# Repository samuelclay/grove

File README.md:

Grove
=====

Mailing list: grove-electronics@googlegroups.com

# Boards

1) Main board - Teensy shield
    - 4 x 3 pins for 144/m 5m strips on trunk
    - 4 x 5 pins (power + rgb) for dispatcher board
    - 3 pins (power + data) for breathing sensor
    - Power switch
    - PTC fuse + zener diode
    - 4 pins for buck converter, 12V -> 5V
    
2) Sensor board
    - 3 pins from mainboard (power, data)
    - Proximity sensor (SI1143x)
    - IR motion detector
    - "breathing" sensor
    - active LEDs

3) Dispatcher board
    - 4 x 5 pins input (power + rgb)
    - 4 PicoBucks (six pins in, six pins out)
    - 16 x 6 pin RGB LEDs (r±, g±, b±)

# Concerns

1) Power
    - 12V deep cycle marine batteries
    - Charging circuit
    - Solar array
    - Delivering 12V to each tree (voltage drop)
2) Firmware
    - Performance over time
    - Running 4x trunks vs 1 trunk 4 times
3) Lighting
    - Soldering high current LEDs
    - 144/m 5m vs splicing power

# Timeline

- May 31: Initial meeting
- June 8th: Dispatcher board rev #1 sent to printer
- June 9th: Main board rev #1 sent to printer
- June 10th: Sensor board rev #1 sent to printer
- July 1st: Boards return from printer, soldering begins
- July 6th: Final board revisions sent to printer
- July 27th: Final boards return from printer, soldering begins
- August 20th: Installation begins on playa
- August 28th: Burning Man begins

# Useful links:

Grove proposal: https://docs.google.com/presentation/d/1Oe51Et6uq_moFoTw9EoB07Vlh8WwSTc89PW6PQpZ1io/edit#slide=id.g12e5fa7d1f_0_1
Grove budget: https://docs.google.com/spreadsheets/d/1ltcCgIae5ANJpvHL2A5ckWDxvADcpXeD_jZIF5hPCvg/edit#gid=0
Prototypes and earlier installation: https://cambridge.nuvustudio.com/studios/grove#tab-proposal-url

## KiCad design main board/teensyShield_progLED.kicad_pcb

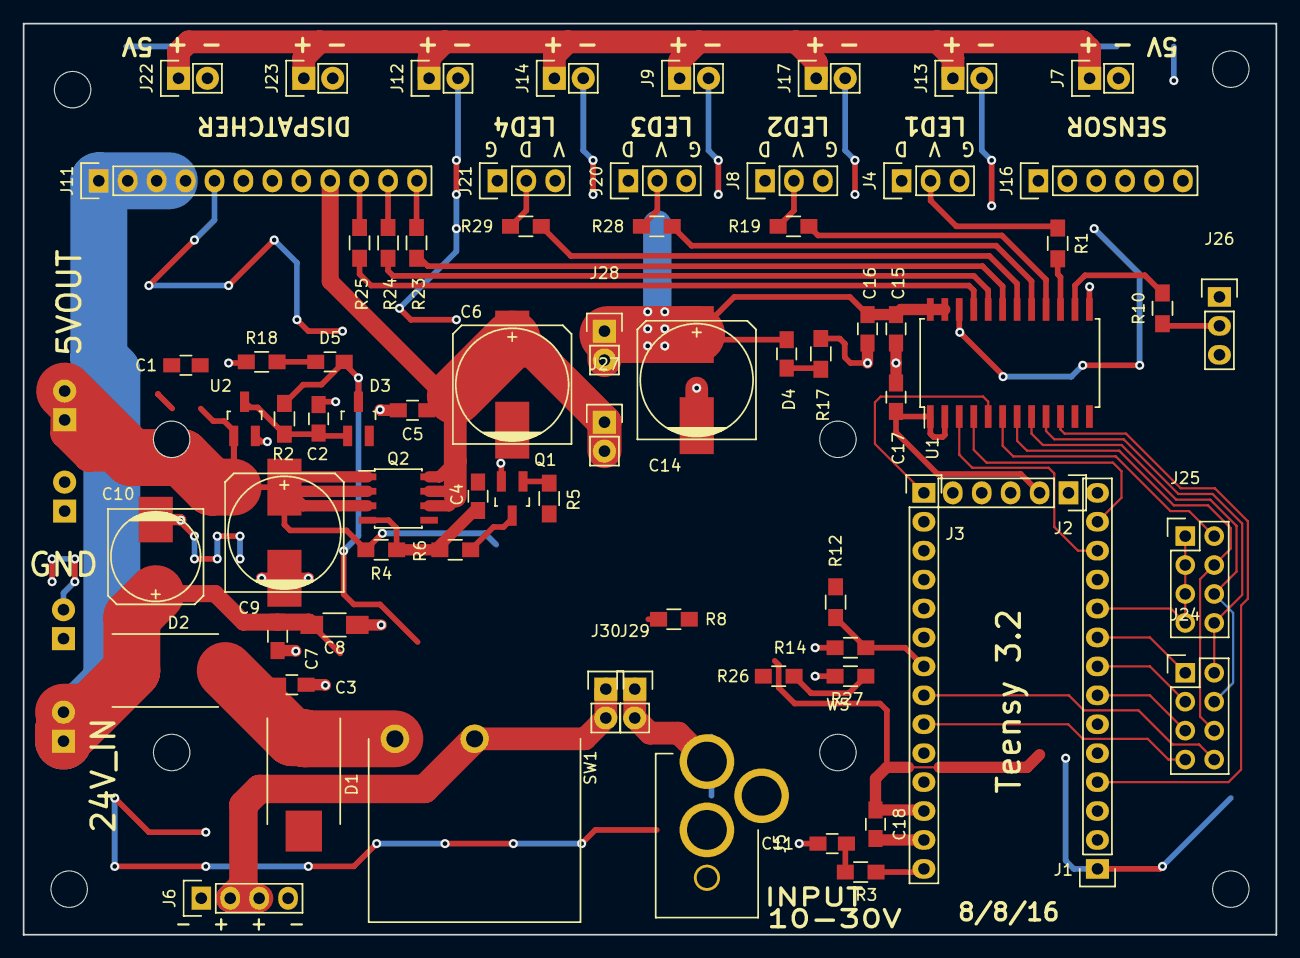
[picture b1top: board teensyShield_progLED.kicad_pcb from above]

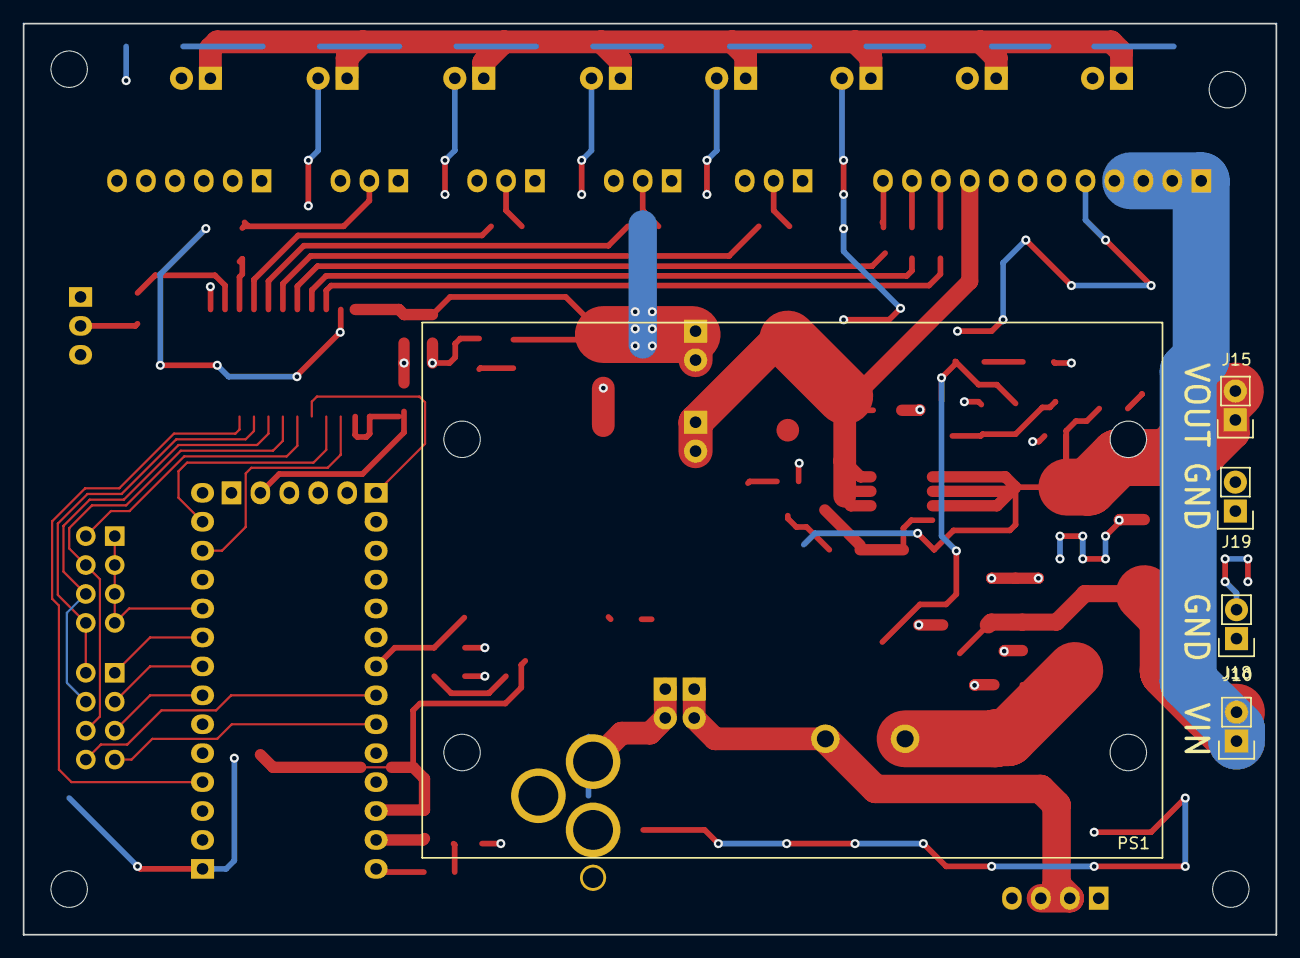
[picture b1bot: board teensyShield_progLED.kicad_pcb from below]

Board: 2 copper layers, 110.0 x 80.0 mm, 85 parts (5 on the bottom side), 52 nets.

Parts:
C1, C2, C3, C5, C7, C11, C15, C16, C17, C18: 1u, 0805; C_0805_HandSoldering
C4: DNS; C_0805_HandSoldering
C6, C10, C14: 1000u, 10V; c_elec_10x10
C8: 10u, 1206; C_1206_HandSoldering
C9: 220u, 35V; c_elec_8x10
D1: TVS; DO-214AB_Handsoldering
D2: SL44HE3_A/H; DO-214AB_Handsoldering
D3: PMEG2005ET,215; SOT-23_DIODE_Handsoldering
D4: BLUE; C_0805_HandSoldering
D5: GRN; C_0805_HandSoldering
J1, J3: CONN_01X14; Pin_Header_Straight_1x14
J2: CONN_01X05; Pin_Header_Straight_1x05
J4, J8, J20, J21, J26: CONN_01X03; Pin_Header_Straight_1x03
J5: BARREL_JACK; PJ-050AH
J6: CONN_01X04; Pin_Header_Straight_1x04
J7, J9, J10, J12, J13, J14, J15, J17, J18, J19, J22, J23, J27, J28, J29, J30: CONN_01X02; Pin_Header_Straight_1x02
J11: CONN_01X12; Pin_Header_Straight_1x12
J16: CONN_01X06; Pin_Header_Straight_1x06
J24, J25: CONN_02X04; Pin_Header_Straight_2x04
PS1: PS_BUCK_MODULE; TC43200
Q1: Q_NMOS_GSD; SOT-23_Handsoldering
Q2: Q_PMOS_SO8; SOIC-8_3.9x4.9mm_Pitch1.27mm
R1, R10, R17, R19, R28, R29: 220; R_0805_HandSoldering
R2: 0; R_0805_HandSoldering
R3, R5, R8, R18: DNS; R_0805_HandSoldering
R4, R12, R14: 10k; R_0805_HandSoldering
R6: 100; R_0805_HandSoldering
R23, R24, R25: 10; R_0805_HandSoldering
R26, R27: 1MEG; R_0805_HandSoldering
SW1: SPST; R1966ABLKBLKFR
U1: SN74LVC8T245PWR; SOIC-24_7.5x15.4mm_Pitch1.27mm
U2: MCP1700T-3302E/TT; SOT-23_Handsoldering
W1, W2, W3, W4, W5, W6, W7, W8: TEST_1P; MountingHole_3.2mm_M3

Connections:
+3V3: C17.1, C18.1, D3.1, D5.2, J2.2, J3.12, R2.1, R8.2, U1.1, U1.2
+5V: C1.1, C10.1, C11.1, J15.1, J15.2, Q2.1, Q2.2, Q2.3, R3.2, R4.2, U2.1
+5VP: C14.1, C15.1, C16.1, D4.2, J4.1, J7.1, J8.1, J9.1, J12.1, J13.1, J14.1, J16.1, J17.1, J20.1, J21.1, J22.1, J23.1, J26.1, J28.1, J28.2, R12.2, U1.23, U1.24
/3V3REG: C2.1, D3.2, R2.2, U2.3
/5V_LSW: C4.1, C5.1, C6.1, J11.9, J27.1, J27.2, Q2.5, Q2.6, Q2.7, Q2.8
/24V_IN: J5.1, J29.1, J29.2
/24V_IN_J: J6.2, J6.3, J30.1, J30.2, SW1.2
/24V_IN_SWITCHED: C3.1, D1.1, D2.2, SW1.1
/24V_IN_SW_RVP: C7.1, C8.1, C9.1, D2.1, J10.1, J10.2, J11.1, J11.2, J11.3, J11.4, R26.2
/CLK_5V: J11.12, R23.1
/CS_5V: J11.10, R25.1
/D4K: D4.1, R17.2
/D5K: D5.1, R18.2
/LED1_5V_STEM: R10.2, U1.14
/LED3_3V3: J24.2, J25.8, U1.9
/LED3_5V: R1.2, U1.15
/LED4_3V3: J25.2, U1.6
/LED4_5V: R29.2, U1.18
/LED5_3V3: J24.4, J25.6, U1.8
/LED5_5V: R19.2, U1.16
/LED8_3V3: J24.6, J25.4, U1.7
/LED8_5V: R28.2, U1.17
/LED_DOUT1: J4.2, R1.1
/LED_DOUT2: J8.2, R19.1
/LED_DOUT3: J20.2, R28.1
/LED_DOUT4: J21.2, R29.1
/LED_DOUT5: J26.2, R10.1
/MOSI_5V: J11.11, R24.1
/P0_RX1: J1.2, J16.5
/P1_TX1: J1.3, J16.4
/P2_LED1: J1.4, U1.10
/P2_P23: J3.11, J16.3
/P5_LED8: J1.7, J24.5
/P6_LED5: J1.8, J24.3
/P7_LED3: J1.9, J24.1
/P8_LED4: J1.10, J25.1, J25.3, J25.5, J25.7
/P10_CS: J1.12, U1.3
/P10_CS_5V: R25.2, U1.21
/P11_MOSI: J1.13, U1.4
/P11_MOSI_5V: R24.2, U1.20
/P13_SCK: J3.1, U1.5
/P14_SCK_5V: R23.2, U1.19
/P15_RES: J3.3, J3.4
/P18: J3.6, Q1.1, R5.2, R8.1
/P19_A5: J3.7, R12.1, R14.2
/P20_A6: R26.1, R27.2
/P20_LED6: J3.8, J24.8
/P21_LED7: J3.9, J24.7
/Q2G: C4.2, Q2.4, R4.1, R6.2
/Q2GR: Q1.3, R6.1
/VIN: J3.14, R3.1
GND: C1.2, C2.2, C3.2, C5.2, C6.2, C7.2, C8.2, C9.2, C10.2, C11.2, C14.2, C15.2, C16.2, C17.2, C18.2, D1.2, J1.1, J2.3, J3.13, J4.3, J5.2, J5.3, J6.1, J6.4, J7.2, J8.3, J9.2, J11.5, J11.6, J11.7, J11.8, J12.2, J13.2, J14.2, J16.2, J16.6, J17.2, J18.1, J18.2, J19.1, J19.2, J20.3, J21.3, J22.2, J23.2, J26.3, Q1.2, R5.1, R14.1, R17.1, R18.1, R27.1, U1.11, U1.12, U1.13, U1.22, U2.2, W1.1, W2.1, W3.1, W4.1, W5.1, W6.1, W7.1, W8.1

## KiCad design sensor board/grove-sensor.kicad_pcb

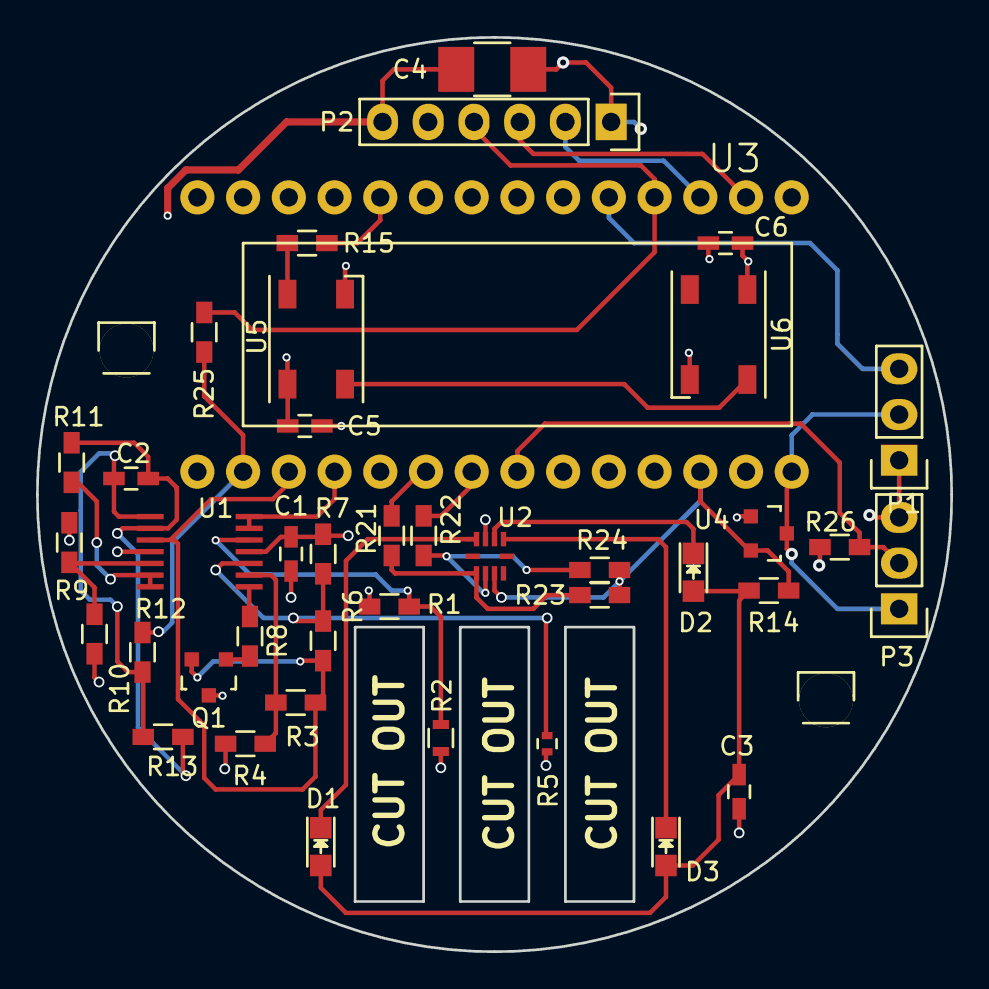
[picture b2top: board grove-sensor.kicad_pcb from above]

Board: 4 copper layers, 50.8 x 50.8 mm, 42 parts (0 on the bottom side), 31 nets.

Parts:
C1, C5, C6: 0.1uF; C_0603_HandSoldering
C2: 10uF; C_0603_HandSoldering
C3: 15uF; C_0603_HandSoldering
C4: 100uF; C_1210_HandSoldering
D1, D2, D3: LED; LED_0805
P1, P3: CONN_01X03; Pin_Header_Straight_1x03
P2: CONN_01X06; Pin_Header_Straight_1x06
P5, P6: CONN_01X01; Pin_Header_Straight_1x01
Q1: Q_NPN_BEC; SOT-23
R1, R7, R9, R10, R23, R24, R26: 10k; R_0603_HandSoldering
R2: 10k; R_0603
R3, R8, R11, R12: 2k; R_0603_HandSoldering
R4: 165k; R_0603_HandSoldering
R5: THERM; R_0402
R6: 1; R_0603_HandSoldering
R13: 4.3k; R_0603_HandSoldering
R14: 30; R_0603_HandSoldering
R15: 300; R_0603_HandSoldering
R21, R22, R25: 0; R_0603_HandSoldering
U1: ADD8704; TSSOP-14
U2: SI1143
U3: Teensy_3.1; Teensy-3.1
U4: MCP1700; SOT-23
U5, U6: WS2812B; LED_WS2812B-PLCC4

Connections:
+5V: C1.1, C4.1, C5.1, C6.1, P1.2, P2.6, P3.1, Q1.3, R1.1, R7.1, R9.1, U1.4, U3.26, U4.3, U5.1, U6.1
/3.3V: R14.1, R23.2, R24.2, U2.3, U3.24, U4.2
/LED_IN: R15.1, U5.4
/OUT: R12.2, R25.2, U3.14
/PIR_IN: P3.2, R26.2, U3.20
/SCL: R22.2, U3.19
/SDA: R21.2, U3.18
/SENSITIVITY: R9.2, R10.1, U1.12
/TEMP_OUT: U1.6, U1.7, U3.16
/V_RAW: Q1.2, R3.1, R6.1, U1.10, U3.15
GND: C1.2, C3.1, C4.2, C5.2, C6.2, P1.1, P2.1, P2.5, P3.3, R2.2, R4.2, R5.2, R10.2, R26.1, U1.11, U2.8, U3.25, U3.27, U4.1, U5.3, U6.3
unnamed: C2.1, R12.1, R13.2, U1.8
unnamed: C2.2, R11.2, R13.1, U1.9
unnamed: C3.2, D1.2, D2.2, D3.2, R14.2
unnamed: D1.1, U2.9
unnamed: D2.1, U2.7
unnamed: D3.1, U2.6
unnamed: P1.3, U3.3
unnamed: P2.2, U3.1
unnamed: P2.3, U3.0
unnamed: P2.4, R25.1, U3.2
unnamed: Q1.1, R8.1
unnamed: R1.2, R2.1, U1.5
unnamed: R3.2, R4.1, U1.2
unnamed: R5.1, R6.2, R7.2, U1.3
unnamed: R8.2, U1.1
unnamed: R11.1, U1.13, U1.14
unnamed: R15.2, U3.8
unnamed: R21.1, R23.1, U2.1
unnamed: R22.1, R24.1, U2.2
unnamed: U5.2, U6.4

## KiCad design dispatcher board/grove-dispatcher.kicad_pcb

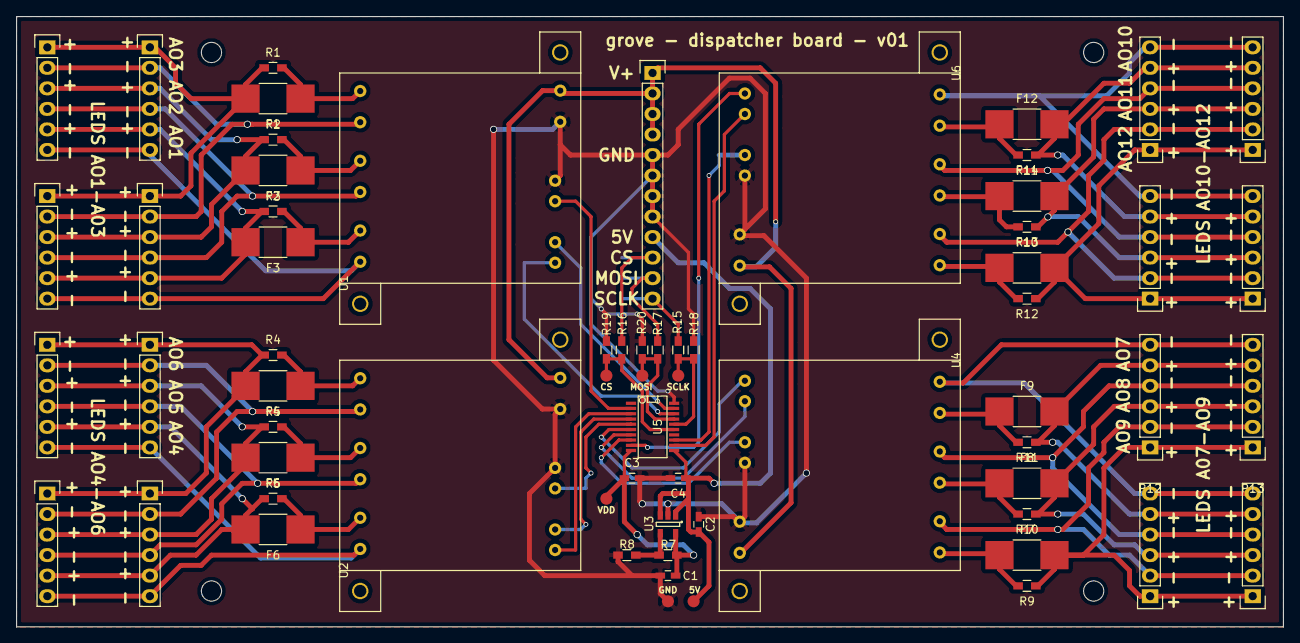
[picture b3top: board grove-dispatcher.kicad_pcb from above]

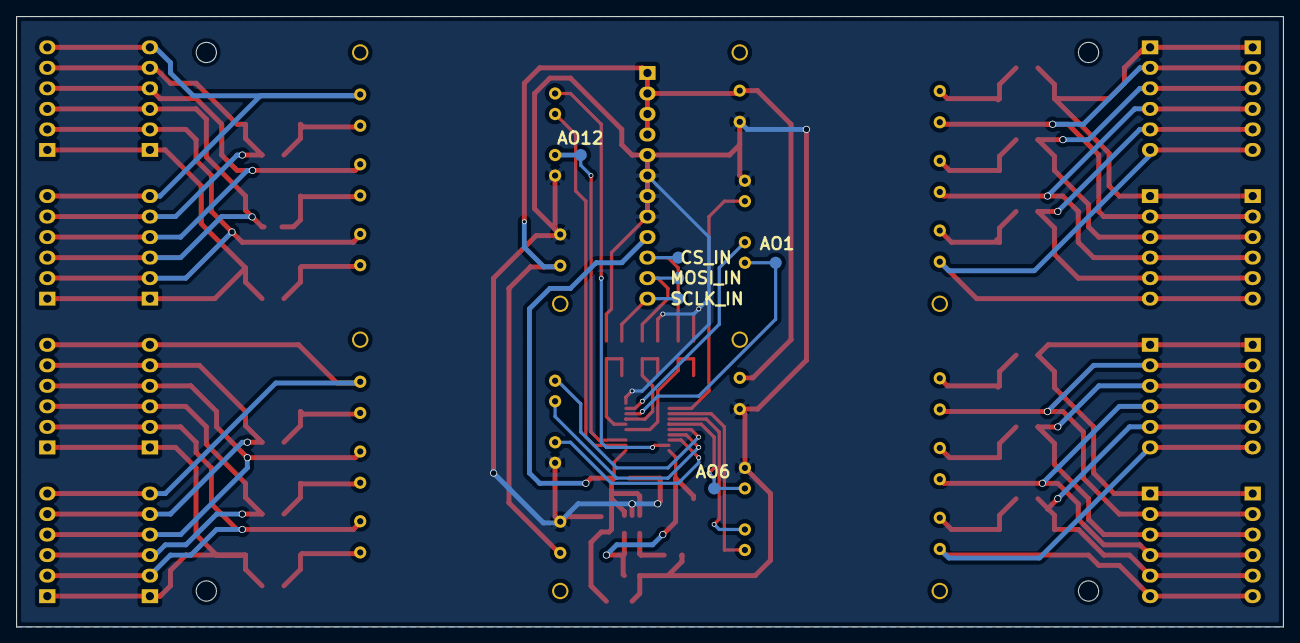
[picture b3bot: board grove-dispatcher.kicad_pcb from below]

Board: 2 copper layers, 156.8 x 75.6 mm, 71 parts (6 on the bottom side), 59 nets.

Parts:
C1, C2, C3, C4: 1uF; C_0603_HandSoldering
F1, F2, F3, F4, F5, F6, F7, F8, F9, F10, F11, F12: PTC; R_1812_HandSoldering
P1: CONN_01X12; Pin_Header_Straight_1x12
P2, P3, P4, P5, P6, P7, P8, P9, P10, P11, P12, P13, P14, P15, P16, P17: CONN_01X06; Pin_Header_Straight_1x06
R1, R2, R3, R4, R5, R6, R9, R10, R11, R12, R13, R14: 0; R_0603_HandSoldering
R7: ?ohm; R_0603_HandSoldering
R8: ?ohms; R_0603_HandSoldering
R15, R16, R17: 10ohm; R_0603_HandSoldering
R18, R19, R20: 1kOhm; R_0603_HandSoldering
U1, U2, U4, U6: PICO_BUCK
U3: NCP603 ADJ / LD3985G25R; SOT-23-5
U5: BH2221FV; SSOP-20
W1: SCLK; Measurement_Point_Round-SMD-Pad_Small
W2: MOSI; Measurement_Point_Round-SMD-Pad_Small
W3: CS; Measurement_Point_Round-SMD-Pad_Small
W4: 5V; Measurement_Point_Round-SMD-Pad_Small
W5: 2V5; Measurement_Point_Round-SMD-Pad_Small
W6: GND; Measurement_Point_Round-SMD-Pad_Small
W7: AO1; Measurement_Point_Round-SMD-Pad_Small
W8: AO6; Measurement_Point_Round-SMD-Pad_Small
W9: AO12; Measurement_Point_Round-SMD-Pad_Small
W10: SCLK_F; Measurement_Point_Round-SMD-Pad_Small
W11: CS_F; Measurement_Point_Round-SMD-Pad_Small
W12: MOSI_F; Measurement_Point_Round-SMD-Pad_Small

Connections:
+2V5: C1.1, C3.1, R7.1, U3.5, U5.10, W5.1
+5V: C2.1, C4.1, P1.9, U3.1, U3.3, U5.11, W4.1
/AO1: U1.0, U5.18, W7.1
/AO2: U1.1, U5.19
/AO3: U1.2, U5.2
/AO4: U2.0, U5.3
/AO5: U2.1, U5.4
/AO6: U2.2, U5.5, W8.1
/AO7: U4.0, U5.6
/AO8: U4.1, U5.7
/AO9: U4.2, U5.8
/AO10: U5.9, U6.0
/AO11: U5.12, U6.1
/AO12: U5.13, U6.2, W9.1
/CS_5V: P1.10, R16.2, W3.1
/CS_IN: R16.1, R19.1, U5.15, W11.1
/MOSI_5V: P1.11, R17.2, W2.1
/MOSI_IN: R17.1, R20.1, U5.17, W12.1
/SCLK_5V: P1.12, R15.2, W1.1
/SCLK_IN: R15.1, R18.1, U5.16, W10.1
/V+: P1.1, P1.2, P1.3, P1.4, U1.5, U2.5, U4.5, U6.5
GND: C1.2, C2.2, C3.2, C4.2, P1.5, P1.6, P1.7, P1.8, R8.2, R18.2, R19.2, R20.2, U1.3, U1.4, U2.3, U2.4, U3.2, U4.3, U4.4, U5.20, U6.3, U6.4, W6.1
unnamed: F1.1, R1.2, U1.6
unnamed: F1.2, P2.1, P3.1, P4.1, P5.1, R1.1
unnamed: F2.1, R2.2, U1.8
unnamed: F2.2, P2.3, P3.3, P4.3, P5.3, R2.1
unnamed: F3.1, R3.2, U1.10
unnamed: F3.2, P2.5, P3.5, P4.5, P5.5, R3.1
unnamed: F4.1, R4.2, U2.6
unnamed: F4.2, P6.1, P7.1, P8.1, P9.1, R4.1
unnamed: F5.1, R5.2, U2.8
unnamed: F5.2, P6.3, P7.3, P8.3, P9.3, R5.1
unnamed: F6.1, R6.2, U2.10
unnamed: F6.2, P6.5, P7.5, P8.5, P9.5, R6.1
unnamed: F7.1, R9.2, U4.6
unnamed: F7.2, P10.1, P11.1, P12.1, P13.1, R9.1
unnamed: F8.1, R10.2, U4.8
unnamed: F8.2, P10.3, P11.3, P12.3, P13.3, R10.1
unnamed: F9.1, R11.2, U4.10
unnamed: F9.2, P10.5, P11.5, P12.5, P13.5, R11.1
unnamed: F10.1, R12.2, U6.6
unnamed: F10.2, P14.1, P15.1, P16.1, P17.1, R12.1
unnamed: F11.1, R13.2, U6.8
unnamed: F11.2, P14.3, P15.3, P16.3, P17.3, R13.1
unnamed: F12.1, R14.2, U6.10
unnamed: F12.2, P14.5, P15.5, P16.5, P17.5, R14.1
unnamed: P2.2, P3.2, P4.2, P5.2, U1.7
unnamed: P2.4, P3.4, P4.4, P5.4, U1.9
unnamed: P2.6, P3.6, P4.6, P5.6, U1.11
unnamed: P6.2, P7.2, P8.2, P9.2, U2.7
unnamed: P6.4, P7.4, P8.4, P9.4, U2.9
unnamed: P6.6, P7.6, P8.6, P9.6, U2.11
unnamed: P10.2, P11.2, P12.2, P13.2, U4.7
unnamed: P10.4, P11.4, P12.4, P13.4, U4.9
unnamed: P10.6, P11.6, P12.6, P13.6, U4.11
unnamed: P14.2, P15.2, P16.2, P17.2, U6.7
unnamed: P14.4, P15.4, P16.4, P17.4, U6.9
unnamed: P14.6, P15.6, P16.6, P17.6, U6.11
unnamed: R7.2, R8.1, U3.4

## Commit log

2016-05-31 Stubbing in Teensy 3.2 makefile and code.
2016-05-31 Stubbing in green drip with end fades. This is our standard cylon.
2016-06-01 Adding random seeding, random colors, and random starts. Looks pretty good!
2016-06-01 Readme
2016-06-01 Moving mainboard firmware into its own directory.
2016-06-01 Stubbing in board directories.
2016-06-01 Whoops, wasn't correctly adjusting offset, created an ever expanding loop. Much better.
2016-06-07 Initial Commit of 2016 Main Board
    Has Teensy connector, input power path, level shifter, LED string connectors, 3V3 regulator.
    TODO: Status LEDs, pick a toggle switch, interface to sensor board, connector for HV LEDs
2016-06-09 Add the sch and libs for the dispatcher so far
2016-06-09 Drop components on the PCB and add fuses
2016-06-09 Some test placement on PCB
2016-06-09 Some tweaks to the gitignore and pcb file
2016-06-10 First pass at routing this simple board
    Conn for LED are spaced far enough apart to allow
    for MTA connectors which are 0.3 inch or more thick
2016-06-10 Add some mounting holes
2016-06-10 Add a silk screen with name and revision
2016-06-13 Sensor footprint.
2016-06-18 Update the lib and sch with new parts
    * DAC now included
    * Added a 2.5V regulator (can be swapped for adj reg)
    to drive VDD so the output range of the DAC is 2.5V
    * Replaced inbound connector with 12 pin
2016-06-18 Update annotations, footprints and net
2016-06-19 Working on PCB some more
2016-06-19 Did all the routing
2016-06-19 Add edge cuts and zones
2016-06-19 Add test points to sch
2016-06-19 Add some test points
2016-06-19 Added mouting holes
2016-06-19 Something changed and I didn't commit it?
2016-06-20 Updated sch with some resistors for the signal pins
2016-06-20 Add layout for resistors + more test points
2016-06-20 Update the pico buck footprint to fix pin placement error
2016-06-21 Final PCB file for Rev1
2016-06-21 Update pin direction on some footprints
2016-06-21 Re add mounting holes
2016-06-21 Fill zones, merge segements and run DRC
2016-06-21 Fix changed connector ordering
2016-06-21 Update silk screen
2016-06-23 Custom components to consolidated lib
2016-06-23 Draft sensor schematic
2016-06-23 Small correction to the pico buck mounting holes
2016-06-23 Rename some nets for debug/documentation
2016-06-23 Drew some footprints and PCB outline
2016-06-24 bunch of sensor stuff
2016-06-24 Update skilscreens
2016-06-24 Fix some hole sizes
2016-06-24 Adjust gerber settings and export
2016-06-24 Small gerber config changes
2016-06-29 Some fixes and placement changes
2016-06-30 Draft sensor route on 4 layers
2016-07-02 Working on some code to test the dispatcher board
    * Add SPI library
    * Setup SPI according to the BH2221FV datasheet
    * Add some bit operation helpers
    * Put color sweep code in main loop
    * temporarily comment out the main neo pixel loop code
    This code is still untested for now
2016-07-04 Working test code
2016-07-07 Revert some test code and add some comments for the dispatcher method
2016-07-07 Fixes and updates to sensor board
2016-07-08 Fixing and adding colors, reversing drip direction, adding randomized drip lengths.
2016-07-08 Adding LED strips back in.
2016-07-11 Added sensor mounting holes
2016-07-14 Temporarily switching pins to match the working DMA pins on the main board.
2016-07-29 Changes for rev 2 of sensor board
2016-08-02 Stubbing in breaths. Fixing blinking bug on head pixel for rest drips.
2016-08-03 Random breaths.
2016-08-03 Testing out dispatcher but not having much luck.
2016-08-03 Curiously, when dispatcher's channel is set to 0, some colors still show up.
2016-08-03 Stubbing in breath position.
2016-08-03 Testing single channel in dispatcher.
2016-08-03 Zeroing out dispatcher.
2016-08-03 Cutting off rest drips when breath takes over.
2016-08-04 Leaves now breath. Still needs rest drip brightener.
2016-08-04 Leaves now breathe and brighten.
2016-08-04 Fixing bug around oddities when a new drip gets made but immediately eaten, resulting in flashing on the leaves.
2016-08-04 Drips are allowed to start while breathing is going.
2016-08-05 Removed old gerbers, added v2
2016-08-05 Just a touch of fade on the back of the breath.
2016-08-06 Adding easing libaries, moving breaths over to easeOutQuad, and rest drips to easeInQuad.
2016-08-08 Adjusting speeds.
2016-08-08 changes req'd for rev b
    Changes:
    - remapped teensy pins to the ones used by the teensy neopixel library
    - added jumper options to connect LED string 4 to all four strings, and disconnect those from the circuit
    - added 5th LED string connector for the sensor stem thing
    - reserved necessary pins
    - removed overcurrent detect circuit because I didn't have a chance to test it, replaced with a PTC footprint which should be lesser risk
2016-08-08 Moving main%20board to main\ board.
2016-08-10 Added test firmware for sensor
2016-08-10 LEDs to show breathing and proximity.
2016-08-10 Pulsing top leaves when breath hits them.
2016-08-14 Showing green in top leaves. May want to reevaluate to minimize color flashes.
2016-08-15 Added ultrasound to sensor and fixed plane short
2016-08-17 Cleanup the dispatcher methods a bit
2016-08-25 5 meters again
2016-08-25 Anticipating the breath by 300ms to sync high currents with top of led strip.
2016-08-25 Adding camp lights and refactoring the crap out of the drips.
2016-08-25 Adding camplight colors.
2016-08-25 Fixing head blink.
2016-08-25 Mainboard v2
2016-08-25 Fixing drip tail when eaten by breath.
2016-08-25 First pass at sensor firmware
2016-08-25 Integrated ultrasound
2016-08-25 Rename some files and setup firmware makefile
2016-08-25 Stubbing in base.
2016-08-25 Working comms with all the sensor
2016-08-25 Playing around with some super basic wind filtering
2016-08-25 Finishing base lighting.
2016-08-25 Test with the servo working
2016-08-25 New breath color.
2016-08-26 Servo code with smooth movement
2016-08-26 Breath sensing
2016-08-26 Run the breath detection on a millis sampling interval (no delay)
2016-08-26 HWSerial comm with the main board
2016-08-26 Breathing now comes form the sensor. Needs tweaking and some PIR sensing.
2016-08-26 PIR hookup tested
2016-08-26 Added state machine flow
2016-08-26 Stubbing in logic to handle proximity state machine from sensor.
2016-08-26 Working state machine
2016-08-26 Tweak some value
2016-08-26 Fade LEDs in/out
2016-08-26 Remove .ino scketches
2016-08-26 Hacking with the IR sensor
2016-08-26 Some cleanup and thresholds
2016-08-26 Fix led fadeout
2016-08-26 Fixing stuck pixel at very bottom.
2016-08-27 Thresholds and prints
2016-08-27 Add the ultrasonic lib
2016-08-27 Various changes:
    * Ultrasonic doesn't reset PIR timeout
    * Probably fix led black issue
    * Open flower at start and then close slowly
2016-08-27 Add ultra lib
2016-08-27 Fix the leds being off
2016-08-27 Update breath sensor to use a diff window
2016-08-27 Switch to remote PIR
2016-08-27 Adding PIR sensors to main board, transmitting to sensor board.
2016-08-28 Fix compile errors
2016-08-29 Fix PIR and change serial prints
2016-08-29 Switch to digital comm on sensor board
2016-08-29 Remove HWSERIAL
2016-08-29 Fixing random breaths.
2016-08-29 Digital comm on mainboard
2016-08-29 Edge trigger only
2016-08-29 Debug inverted pin rx/tx issue
2016-08-29 Remove some prox variable that weren't working
2016-08-29 Tweaking on playa, fixing some bugs with breaths and sensing
2016-08-29 Don't create a new breath every clock cycle when active breathing.
2016-08-29 Adding FAKE_PIR
2016-08-29 Turn off breathing when proximity sensor goes low.
2016-08-30 Turning off fake prox
2016-08-30 Colors of sensor and trunk.
2016-08-30 -comments
2016-08-30 Leaves timing.
2016-08-30 Disable prox for now on flower
2016-09-26 Turning proximity back on.
2018-01-14 Updating teensy.
2018-01-14 Better colors for camplights.
